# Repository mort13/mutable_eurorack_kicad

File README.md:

Mutable Instruments' Eurorack Modules.

Forked from pichenettes' version and identical except:
- Eagle brd and sch files converted to XML (making possible import into KiCad)
- For some modules, KiCad versions have been added

I have updated this repo to reflect upstream changes, but I am no longer able to convert the Eagle files, so not all are available as XML.

* [Blades](http://mutable-instruments.net/modules/blades): Dual multimode filter.
* [Blinds](http://mutable-instruments.net/modules/blinds): Quad VC-polarizer.
* [Braids](http://mutable-instruments.net/modules/braids): Macro-oscillator.
* [Branches](http://mutable-instruments.net/modules/branches): Dual Bernoulli gate.
* [Clouds](http://mutable-instruments.net/modules/clouds): Texture synthesizer.
* [Ears](http://mutable-instruments.net/modules/ears): Contact microphone.
* [Edges](http://mutable-instruments.net/modules/edges): Quad chiptune digital oscillator.
* [Elements](http://mutable-instruments.net/modules/elements): Modal synthesizer.
* [Frames](http://mutable-instruments.net/modules/frames): Keyframer/mixer.
* [Grids](http://mutable-instruments.net/modules/grids): Topographic drum sequencer.
* [Kinks](http://mutable-instruments.net/modules/kinks): Utility module - rectifier, analog logic, S&H, noise.
* [Links](http://mutable-instruments.net/modules/links): Utility module - buffer, mixer.
* [Marbles](http://mutable-instruments.net/modules/marbles): Random sampler.
* [Peaks](http://mutable-instruments.net/modules/peaks): Dual trigger converter.
* [Plaits](http://mutable-instruments.net/modules/plaits): Macro oscillator.
* [Rings](http://mutable-instruments.net/modules/rings): Resonator.
* [Ripples](http://mutable-instruments.net/modules/ripples): Liquid 2-pole BP, 2-pole LP and 4-pole LP filter.
* [Shades](http://mutable-instruments.net/modules/shades): Triple attenuverter.
* [Shelves](http://mutable-instruments.net/modules/shelves): EQ filter.
* [Stages](http://mutable-instruments.net/modules/stages): Segment generator.
* [Streams](http://mutable-instruments.net/modules/streams): Dual dynamics gate.
* [Tides](http://mutable-instruments.net/modules/tides): Tidal modulator.
* [Veils](http://mutable-instruments.net/modules/veils): Quad VCA.
* [Volts](http://mutable-instruments.net/modules/volts): +5V power module.
* [Warps](http://mutable-instruments.net/modules/warps): Meta-modulator.
* [Yarns](http://mutable-instruments.net/modules/yarns): MIDI interface.

License
=======

Code (AVR projects): GPL3.0.

Code (STM32F projects): MIT license.

Hardware: cc-by-sa-3.0

By: Emilie Gillet (emilie.o.gillet@gmail.com)

Guidelines for derivative works
===============================

**Mutable Instruments is a registered trademark.**

The name "Mutable Instruments" should not be used on any of the derivative works you create from these files.

We do not recommend you to keep the original name of the Mutable Instruments module for your derivative works.

For example, your 5U adaptation of Mutable Instruments Clouds can be called "Foobar Modular - Particle Generator".

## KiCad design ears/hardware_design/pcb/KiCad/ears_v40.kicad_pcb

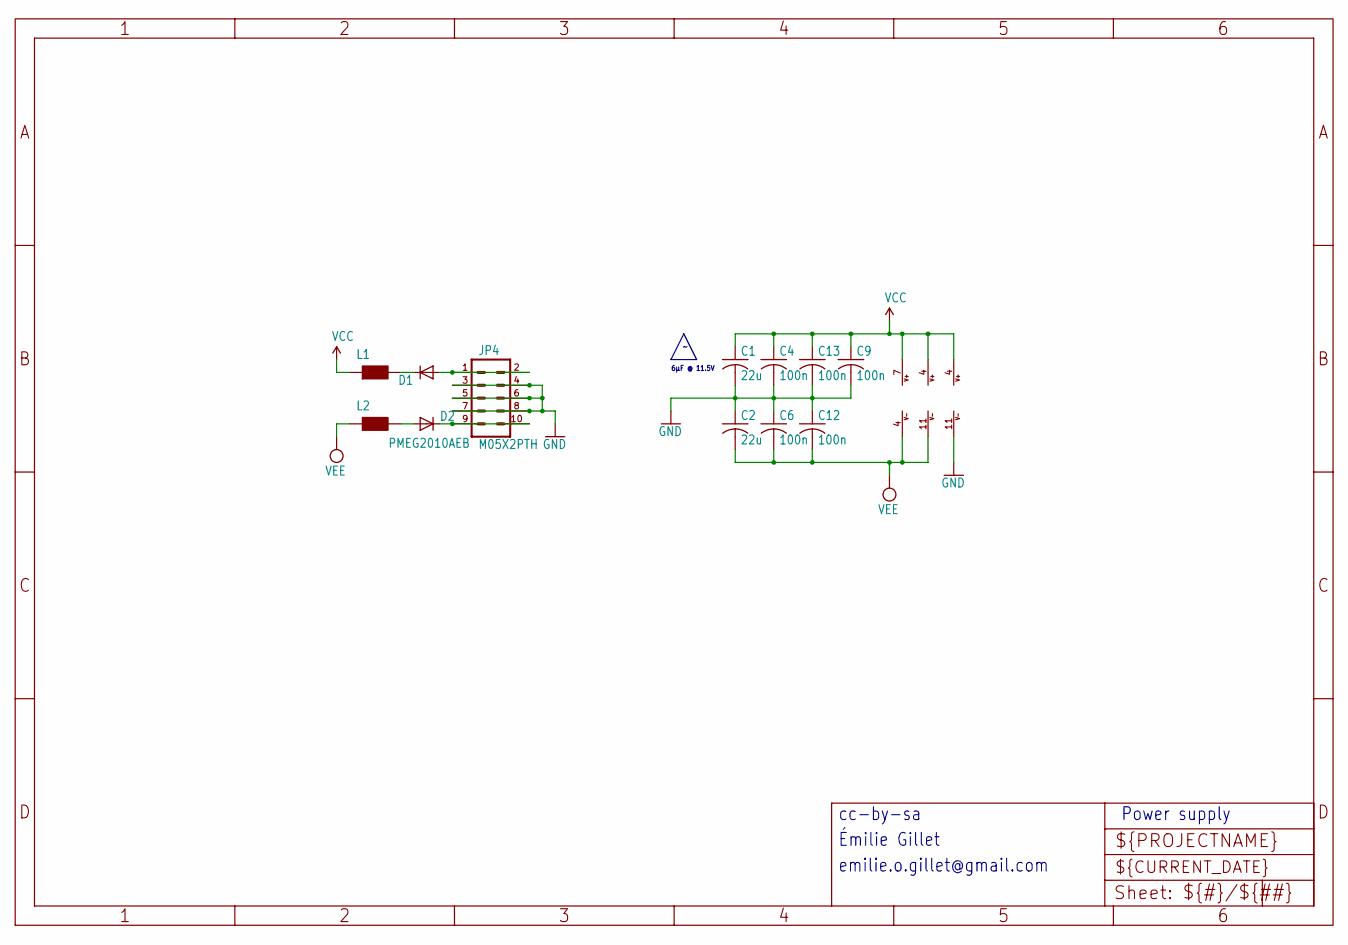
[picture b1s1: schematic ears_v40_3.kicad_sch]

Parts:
C1, C2: 22u; C1206
C4, C6, C9, C12, C13: 100n; C0402
D1, D2: PMEG2010AEB; SOD523
IC1: OPA1641; MSOP8
IC2, IC3: LM324PW; TSSOP14
JP4: M05X2PTH; AVR_ICSP
L1, L2: WE-CBF_0603; 0603

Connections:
GND: C1.2, C2.1, C4.2, C6.1, C9.2, C12.1, C13.2, IC2.11 (V-), JP4.3, JP4.4, JP4.5, JP4.6, JP4.7, JP4.8; also elsewhere on the board
unnamed: D1.A, JP4.1, JP4.2
unnamed: D2.C, JP4.9, JP4.10
unnamed: D1.C, L1.2
unnamed: D2.A, L2.2
VCC: C1.1, C4.1, C9.1, C13.1, IC1.7 (V+), IC2.4 (V+), IC3.4 (V+), L1.1; also elsewhere on the board
VEE: C2.2, C6.2, C12.2, IC1.4 (V-), IC3.11 (V-), L2.1; also elsewhere on the board

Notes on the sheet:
6µF @ 11.5V
cc-by-sa
emilie.o.gillet@gmail.com
Émilie Gillet
Power supply

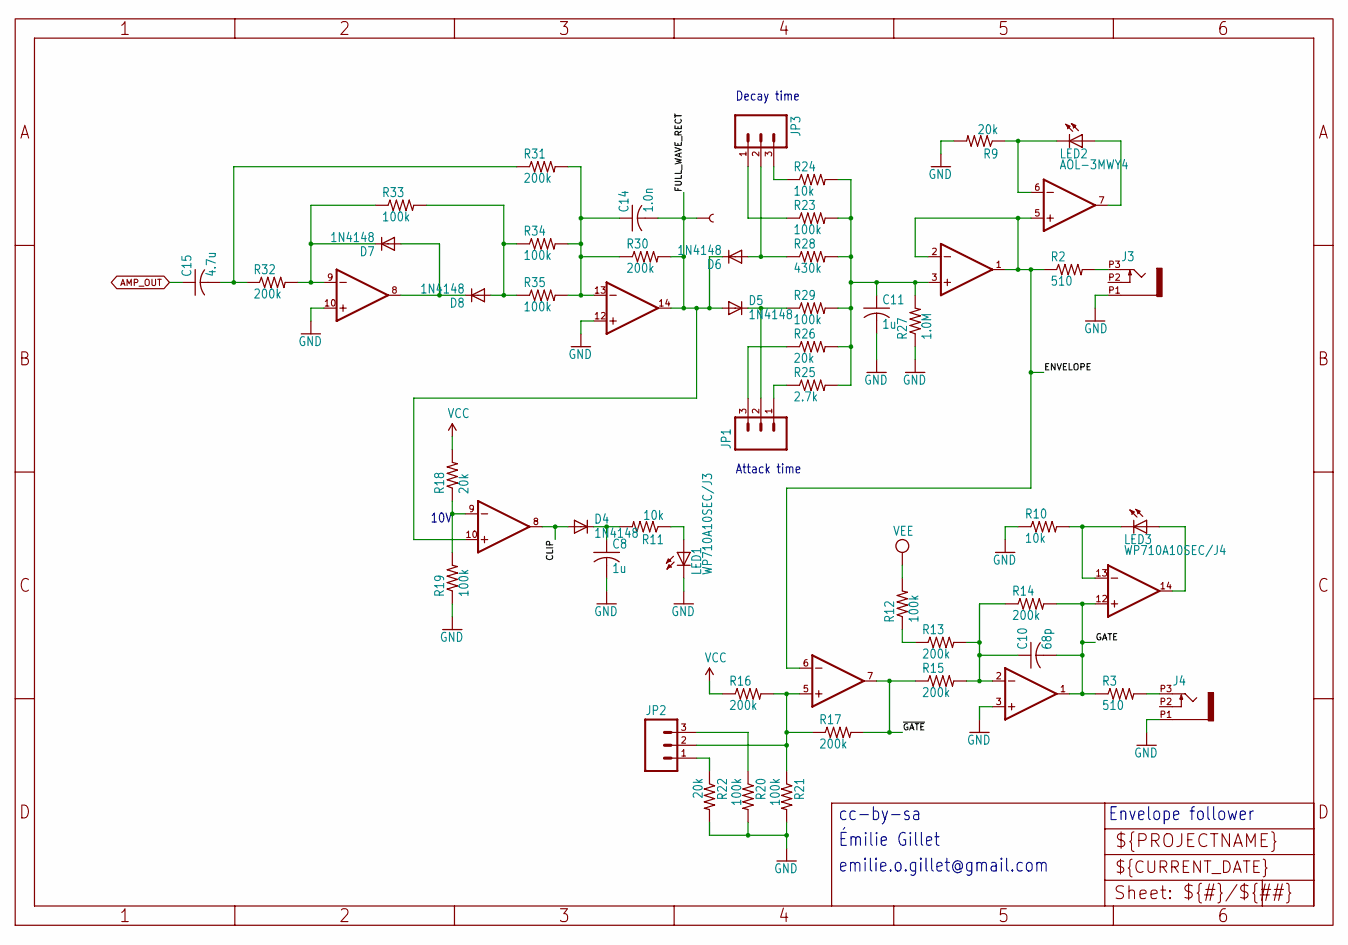
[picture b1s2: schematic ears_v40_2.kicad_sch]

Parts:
C8, C11: 1u; C0402
C10: 68p; C0402
C14: 1.0n; C0402
C15: 4.7u; C0603
D4, D5, D6, D7, D8: 1N4148; SOD523
IC2, IC3: LM324PW; TSSOP14
J3, J4: PJ301_THONKICONN6; WQP_PJ_301M6
JP1, JP2, JP3: M03PTH; 1X03
LED1: WP710A10SEC/J3; LED3MM
LED2: AOL-3MWY4; LED3MM
LED3: WP710A10SEC/J4; LED3MM
R2, R3: 510; R0402
R9, R18, R22, R26: 20k; R0402
R10, R11, R24: 10k; R0402
R12, R19, R20, R21, R23, R29, R33, R34, R35: 100k; R0402
R13, R14, R15, R16, R17, R30, R31, R32: 200k; R0402
R25: 2.7k; R0402
R27: 1.0M; R0402
R28: 430k; R0402
TP1: TEST-POINT3X5; PAD.03X.05

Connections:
AMP_OUT: C15.1; also elsewhere on the board
AMP_OUT_AC: C15.2, R31.1, R32.1
CLIP: D4.A, IC2.8 (OUT)
ENVELOPE: IC2.6 (-IN), IC3.1 (OUT), IC3.2 (-IN), IC3.5 (+IN), R2.1
FULL_WAVE_RECT: C14.2, D5.A, D6.C, IC2.10 (+IN), IC3.14 (OUT), R30.2, TP1.P$1
GATE: C10.2, IC2.1 (OUT), IC2.12 (+IN), R3.1, R14.2
GND: C8.2, C11.2, IC2.3 (+IN), IC3.10 (+IN), IC3.12 (+IN), J3.P1 (1), J4.P1 (1), LED1.K (C), R9.2, R10.1, R19.1, R20.2, R21.2, R22.2, R27.1; also elsewhere on the board
unnamed: D7.A, D8.C, IC3.8 (OUT)
unnamed: C10.1, IC2.2 (-IN), R13.2, R14.1, R15.2
unnamed: D7.C, IC3.9 (-IN), R32.2, R33.1
unnamed: D8.A, R33.2, R34.1, R35.1
unnamed: C14.1, IC3.13 (-IN), R30.1, R31.2, R34.2, R35.2
unnamed: J3.P3 (3), R2.2
unnamed: IC3.6 (-IN), LED2.K (C), R9.1
unnamed: D5.C, JP1.2, R29.1
unnamed: C11.1, IC3.3 (+IN), R23.2, R24.2, R25.2, R26.2, R27.2, R28.2, R29.2
unnamed: JP3.3, R24.1
unnamed: JP3.1, R23.1
unnamed: D6.A, JP3.2, R28.1
unnamed: JP1.1, R25.1
unnamed: JP1.3, R26.1
unnamed: IC2.9 (-IN), R18.1, R19.2
unnamed: C8.1, D4.C, R11.2
unnamed: IC3.7 (OUT), LED2.A
unnamed: LED1.A, R11.1
unnamed: J4.P3 (3), R3.2
unnamed: IC2.5 (+IN), JP2.2, R16.2, R17.1, R21.1
unnamed: JP2.1, R22.1
unnamed: JP2.3, R20.1
unnamed: IC2.13 (-IN), LED3.K (C), R10.2
unnamed: IC2.14 (OUT), LED3.A
unnamed: R12.1, R13.1
VCC: R16.1, R18.2; also elsewhere on the board
VEE: R12.2; also elsewhere on the board
~GATE: IC2.7 (OUT), R15.1, R17.2

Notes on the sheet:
cc-by-sa
10V
emilie.o.gillet@gmail.com
Émilie Gillet
Attack time
Envelope follower
Decay time

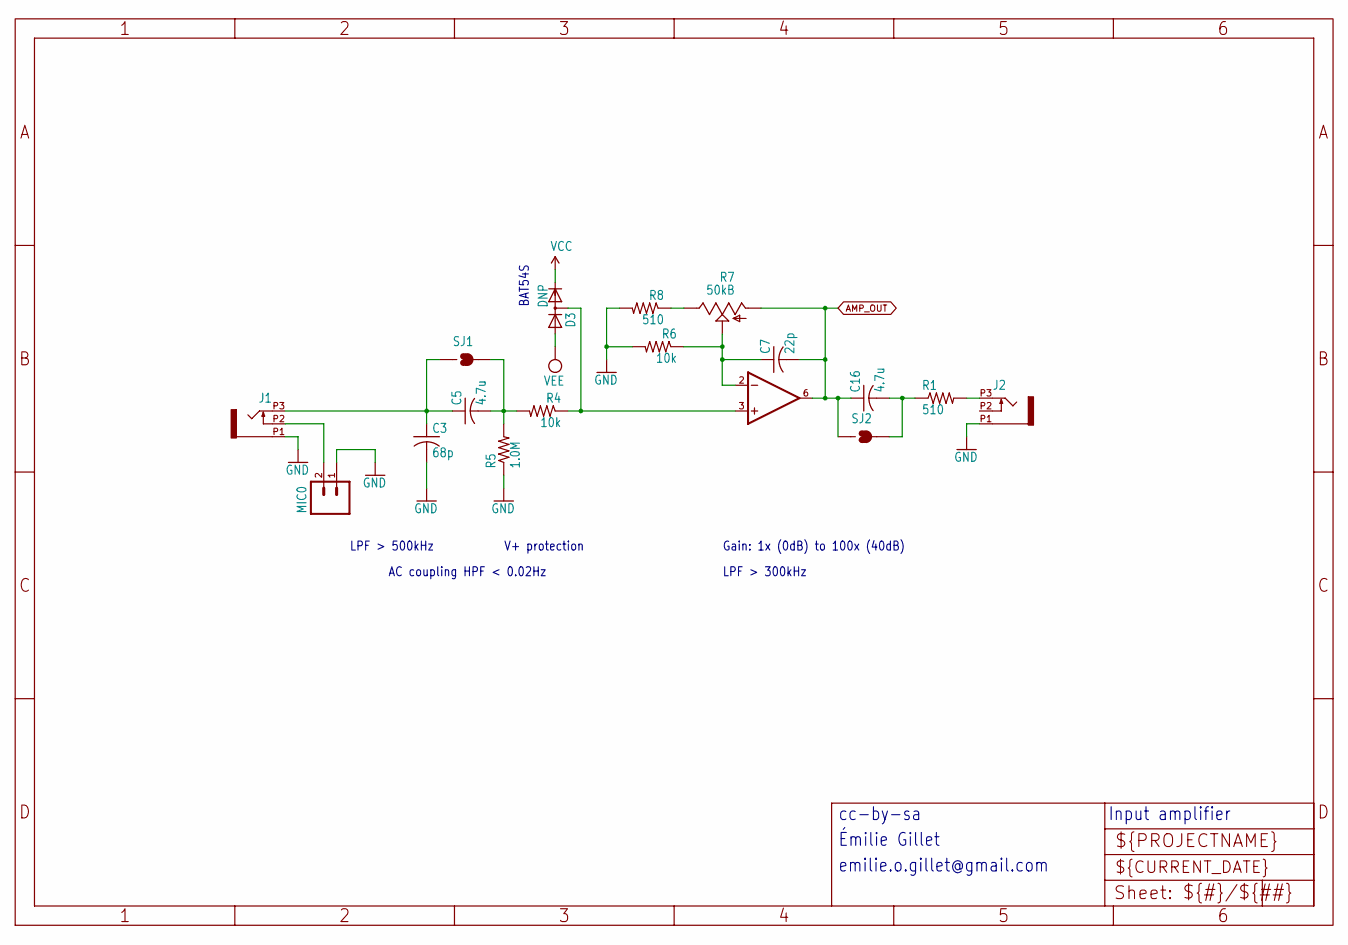
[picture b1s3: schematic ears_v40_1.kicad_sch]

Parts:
C3: 68p; C0402
C5, C16: 4.7u; C0603
C7: 22p; C0402
D3: DNP; SOT23
IC1: OPA1641; MSOP8
J1, J2: PJ301_THONKICONN6; WQP_PJ_301M6
MIC0: M02TINY; 1X02_TINY
R1, R8: 510; R0402
R4, R6: 10k; R0402
R5: 1.0M; R0402
R7: 50kB; ALPS_POT_VERTICAL_PS
SJ1, SJ2: SOLDERJUMPERNC; SJ_2S

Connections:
AMP_OUT: C7.2, C16.1, IC1.6 (OUT), R7.P$3 (A), SJ2.1; also elsewhere on the board
GND: C3.2, J1.P1 (1), J2.P1 (1), MIC0.1, R5.1, R6.2, R8.2; also elsewhere on the board
unnamed: D3.3 (AC), IC1.3 (+IN), R4.1
unnamed: J2.P3 (3), R1.2
unnamed: C3.1, C5.1, J1.P3 (3), SJ1.1
unnamed: J1.P2 (2), MIC0.2
unnamed: C7.1, IC1.2 (-IN), R6.1, R7.P$2 (S)
unnamed: C5.2, R4.2, R5.2, SJ1.2
unnamed: R7.P$1 (E), R8.1
unnamed: C16.2, R1.1, SJ2.2
VCC: D3.2 (C); also elsewhere on the board
VEE: D3.1 (A); also elsewhere on the board

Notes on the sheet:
BAT54S
LPF > 500kHz
AC coupling HPF < 0.02Hz
emilie.o.gillet@gmail.com
LPF > 300kHz
Input amplifier
Gain: 1x (0dB) to 100x (40dB)
Émilie Gillet
cc-by-sa
V+ protection

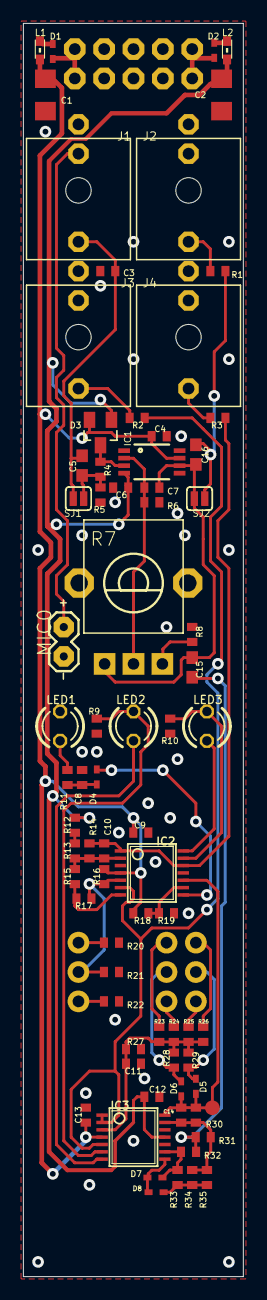
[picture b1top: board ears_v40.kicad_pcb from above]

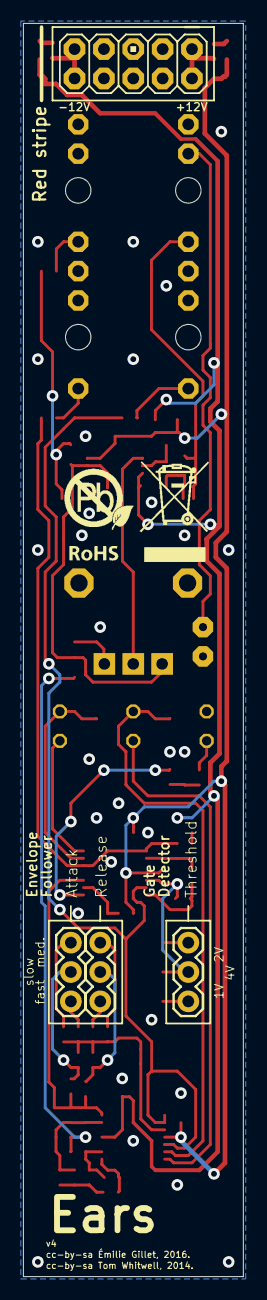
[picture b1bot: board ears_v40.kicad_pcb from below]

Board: 2 copper layers, 19.0 x 108.4 mm, 80 parts (5 on the bottom side), 47 nets.

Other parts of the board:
U$2: ROHS

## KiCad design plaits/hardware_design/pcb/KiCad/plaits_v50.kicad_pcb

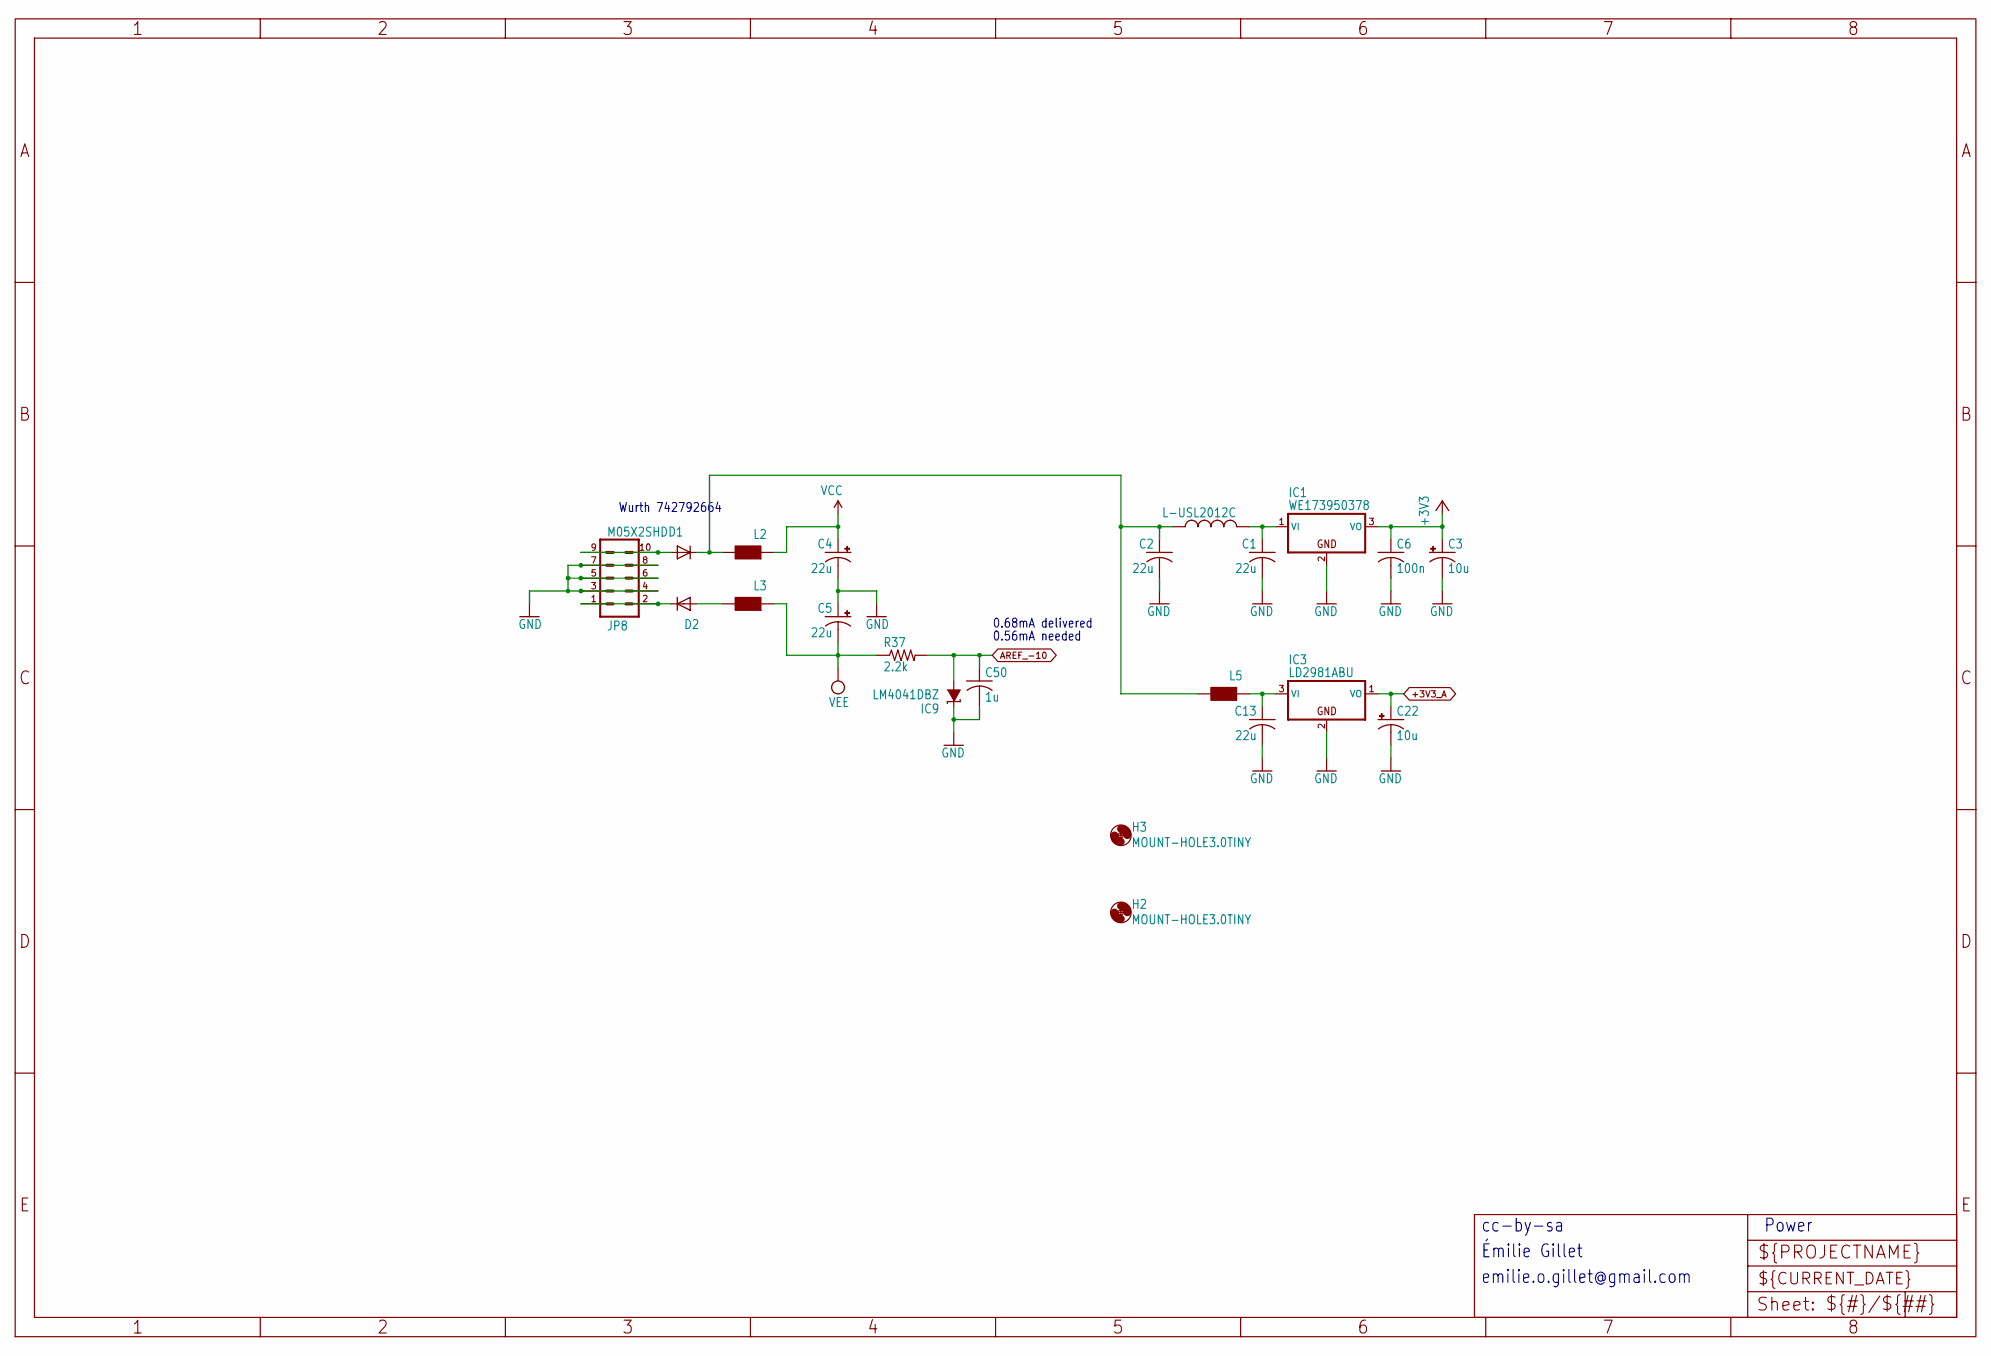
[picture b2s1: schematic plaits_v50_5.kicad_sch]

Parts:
C1, C2, C13: 22u; C1206
C3, C22: 10u; PANASONIC_A
C4, C5: 22u; PANASONIC_B
C6: 100n; C0402
C50: 1u; C0402
D1, D2: 1N5819HW; SOD123
H2, H3: MOUNT-HOLE3.0TINY; 3,0TINY
IC1: WE173950378; WE78
IC3: LD2981ABU; SOT89
IC9: LM4041DBZ; DBZ_R-PDSO-G3
JP8: M05X2SHD; 2X5-SHROUDED
L1: L-USL2012C; L2012C
L2, L3, L5: WE-CBF_0603; 0603
R37: 2.2k; R0402

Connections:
+3V3: C3.+, C6.1, IC1.3 (VO); also elsewhere on the board
+3V3_A: C22.+, IC3.1 (VO); also elsewhere on the board
AREF_-10: C50.1, IC9.2 (A), R37.2; also elsewhere on the board
GND: C1.2, C2.2, C3.-, C4.-, C5.+, C6.2, C13.2, C22.-, C50.2, IC1.2 (GND), IC3.2 (GND), IC9.1 (C), JP8.3, JP8.4, JP8.5, JP8.6, JP8.7, JP8.8; also elsewhere on the board
unnamed: C1.1, IC1.1 (VI), L1.2
unnamed: D2.A, L3.2
unnamed: C2.1, D1.C, L1.1, L2.2, L5.2
unnamed: C13.1, IC3.3 (VI), L5.1
unnamed: D1.A, JP8.9, JP8.10
unnamed: D2.C, JP8.1, JP8.2
VCC: C4.+, L2.1; also elsewhere on the board
VEE: C5.-, L3.1, R37.1; also elsewhere on the board

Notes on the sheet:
emilie.o.gillet@gmail.com
Émilie Gillet
Wurth 742792664
cc-by-sa
Power
0.68mA delivered
0.56mA needed

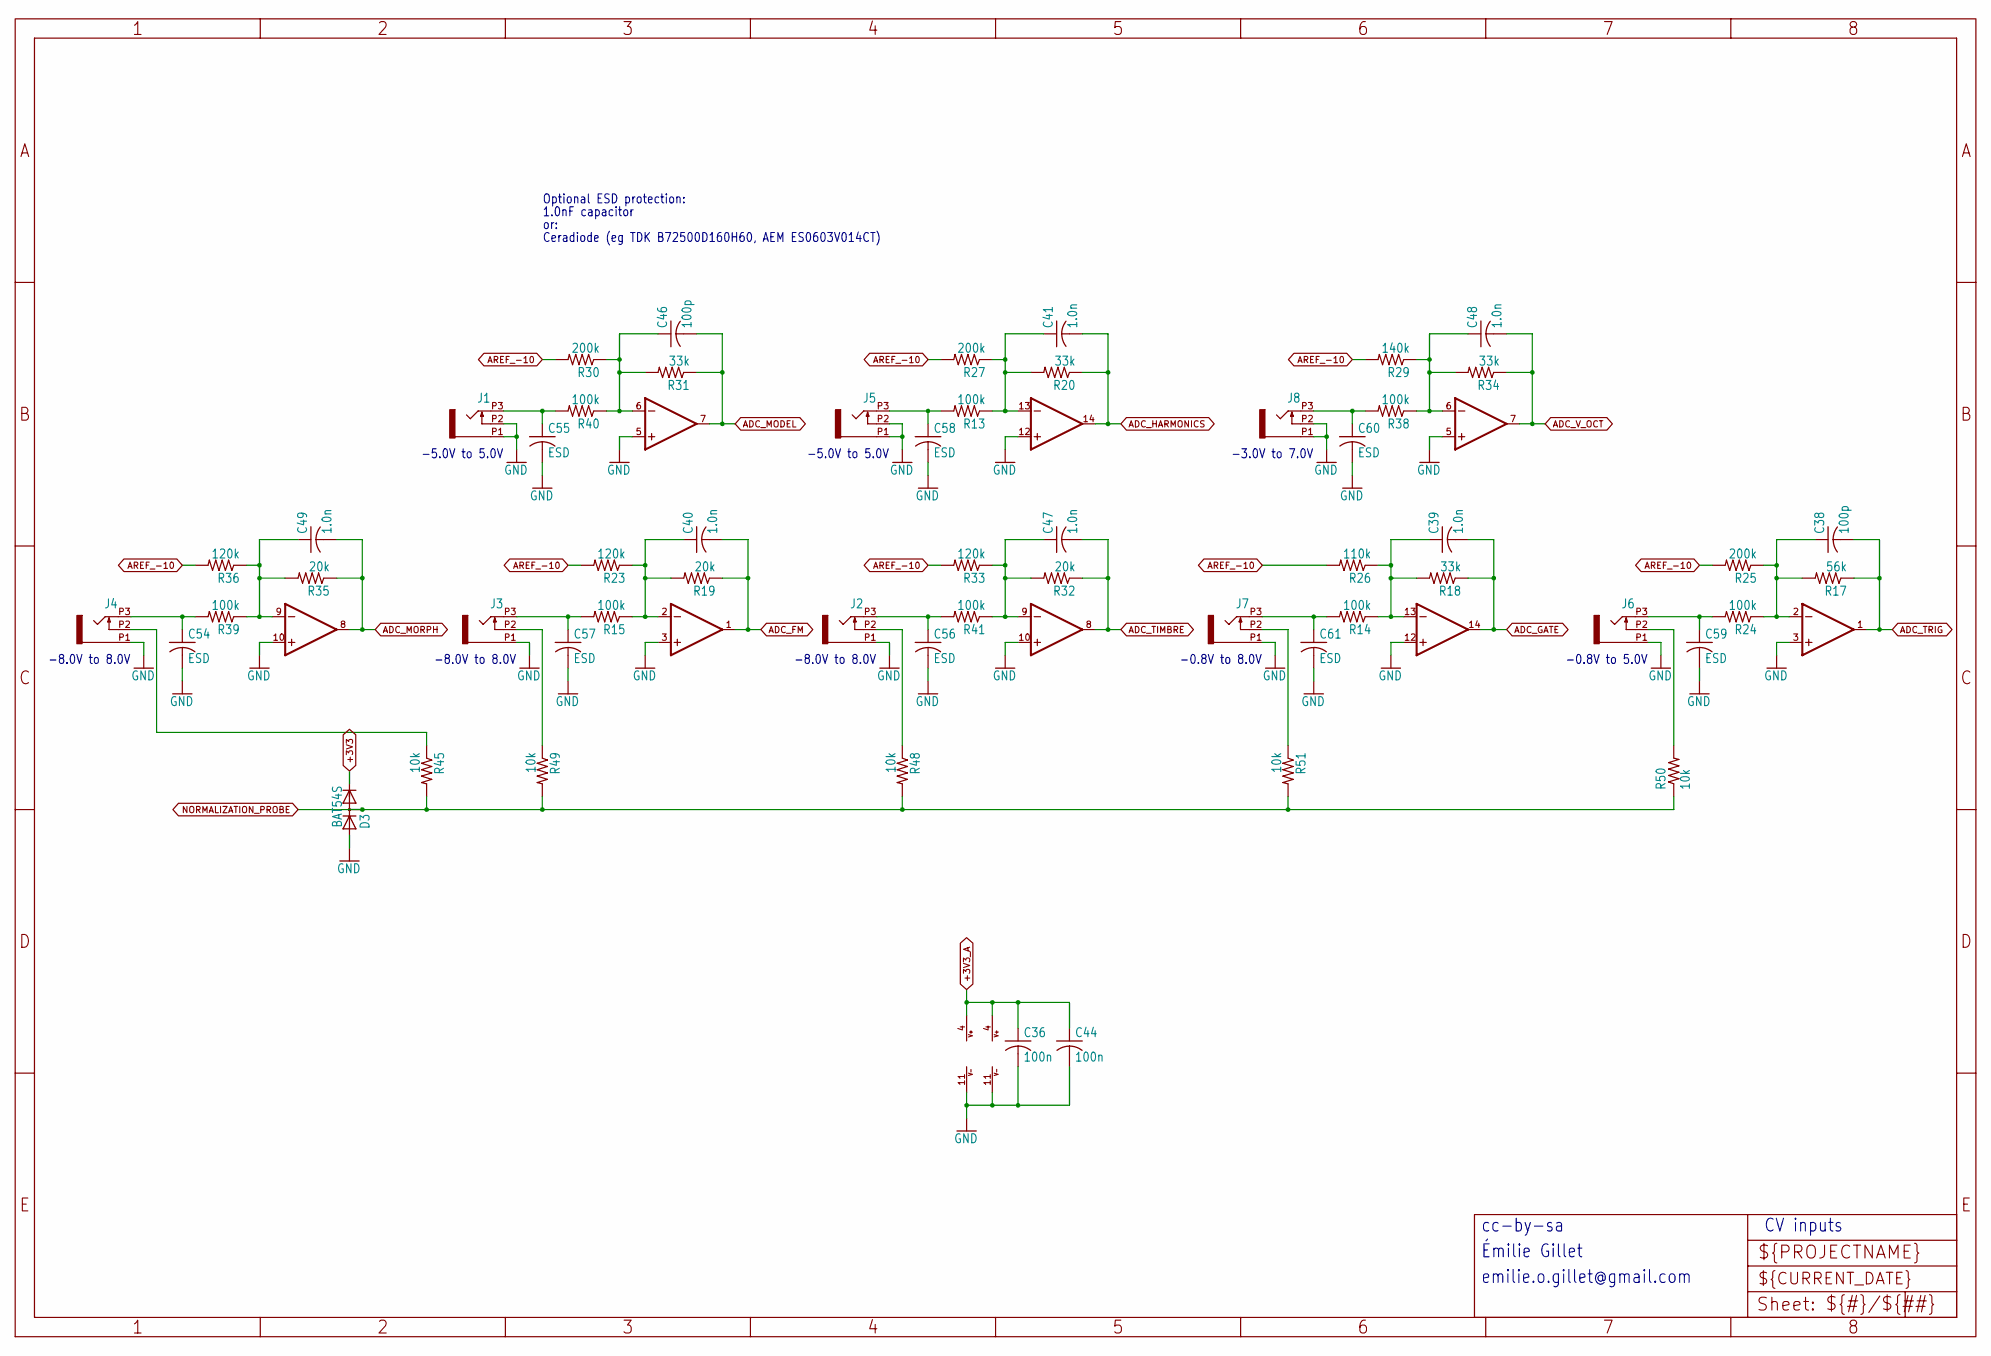
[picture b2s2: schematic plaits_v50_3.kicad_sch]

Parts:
C36, C44: 100n; C0402
C38, C46: 100p; C0402
C39, C40, C41, C47, C48, C49: 1.0n; C0402
C54, C55, C56, C57, C58, C59, C60, C61: ESD; C0603
D3: BAT54S; SOT23
IC6, IC7: TL074PW; TSSOP14_065
J1, J2, J3, J4, J5, J6, J7, J8: PJ301_THONKICONN6; WQP_PJ_301M6
R13, R14, R15, R24, R38, R39, R40, R41: 100k; R0402
R17: 56k; R0402
R18, R20, R31, R34: 33k; R0402
R19, R32, R35: 20k; R0402
R23, R33, R36: 120k; R0402
R25, R27, R30: 200k; R0402
R26: 110k; R0402
R29: 140k; R0402
R45, R48, R49, R50, R51: 10k; R0402

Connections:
+3V3: D3.2 (C); also elsewhere on the board
+3V3_A: C36.1, C44.1, IC6.4 (V+), IC7.4 (V+); also elsewhere on the board
ADC_FM: C40.2, IC7.1 (OUT), R19.1; also elsewhere on the board
ADC_GATE: C39.2, IC6.14 (OUT), R18.1; also elsewhere on the board
ADC_HARMONICS: C41.2, IC7.14 (OUT), R20.1; also elsewhere on the board
ADC_MODEL: C46.2, IC6.7 (OUT), R31.1; also elsewhere on the board
ADC_MORPH: C49.2, IC7.8 (OUT), R35.1; also elsewhere on the board
ADC_TIMBRE: C47.2, IC6.8 (OUT), R32.1; also elsewhere on the board
ADC_TRIG: C38.2, IC6.1 (OUT), R17.1; also elsewhere on the board
ADC_V_OCT: C48.2, IC7.7 (OUT), R34.1; also elsewhere on the board
AREF_-10: R23.2, R25.2, R26.2, R27.2, R29.2, R30.2, R33.2, R36.2; also elsewhere on the board
FM_IN: C57.1, J3.P3 (3), R15.2
GATE_IN: C61.1, J7.P3 (3), R14.2
GATE_IN1: C59.1, J6.P3 (3), R24.2
GND: C36.2, C44.2, C54.2, C55.2, C56.2, C57.2, C58.2, C59.2, C60.2, C61.2, D3.1 (A), IC6.3 (+IN), IC6.5 (+IN), IC6.10 (+IN), IC6.11 (V-), IC6.12 (+IN), IC7.3 (+IN), IC7.5 (+IN), IC7.10 (+IN), IC7.11 (V-), IC7.12 (+IN), J1.P1 (1), J1.P2 (2), J2.P1 (1), J3.P1 (1), J4.P1 (1), J5.P1 (1), J5.P2 (2), J6.P1 (1), J7.P1 (1), J8.P1 (1), J8.P2 (2); also elsewhere on the board
HARMONICS_IN: C58.1, J5.P3 (3), R13.2
MODEL_IN: C55.1, J1.P3 (3), R40.2
MORPH_IN: C54.1, J4.P3 (3), R39.2
unnamed: J6.P2 (2), R50.2
unnamed: C38.1, IC6.2 (-IN), R17.2, R24.1, R25.1
unnamed: J3.P2 (2), R49.1
unnamed: J2.P2 (2), R48.1
unnamed: J4.P2 (2), R45.1
unnamed: C39.1, IC6.13 (-IN), R14.1, R18.2, R26.1
unnamed: C48.1, IC7.6 (-IN), R29.1, R34.2, R38.1
unnamed: C56.1, J2.P3 (3), R41.2
unnamed: C49.1, IC7.9 (-IN), R35.2, R36.1, R39.1
unnamed: C40.1, IC7.2 (-IN), R15.1, R19.2, R23.1
unnamed: J7.P2 (2), R51.1
unnamed: C46.1, IC6.6 (-IN), R30.1, R31.2, R40.1
unnamed: C47.1, IC6.9 (-IN), R32.2, R33.1, R41.1
unnamed: C41.1, IC7.13 (-IN), R13.1, R20.2, R27.1
NORMALIZATION_PROBE: D3.3 (AC), R45.2, R48.2, R49.2, R50.1, R51.2; also elsewhere on the board
V_OCT_IN: C60.1, J8.P3 (3), R38.2

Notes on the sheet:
Émilie Gillet
-8.0V to 8.0V
CV inputs
Optional ESD protection:
or:
emilie.o.gillet@gmail.com
cc-by-sa
-5.0V to 5.0V
-3.0V to 7.0V
Ceradiode (eg TDK B72500D160H60, AEM ES0603V014CT)
-0.8V to 5.0V
1.0nF capacitor
-0.8V to 8.0V

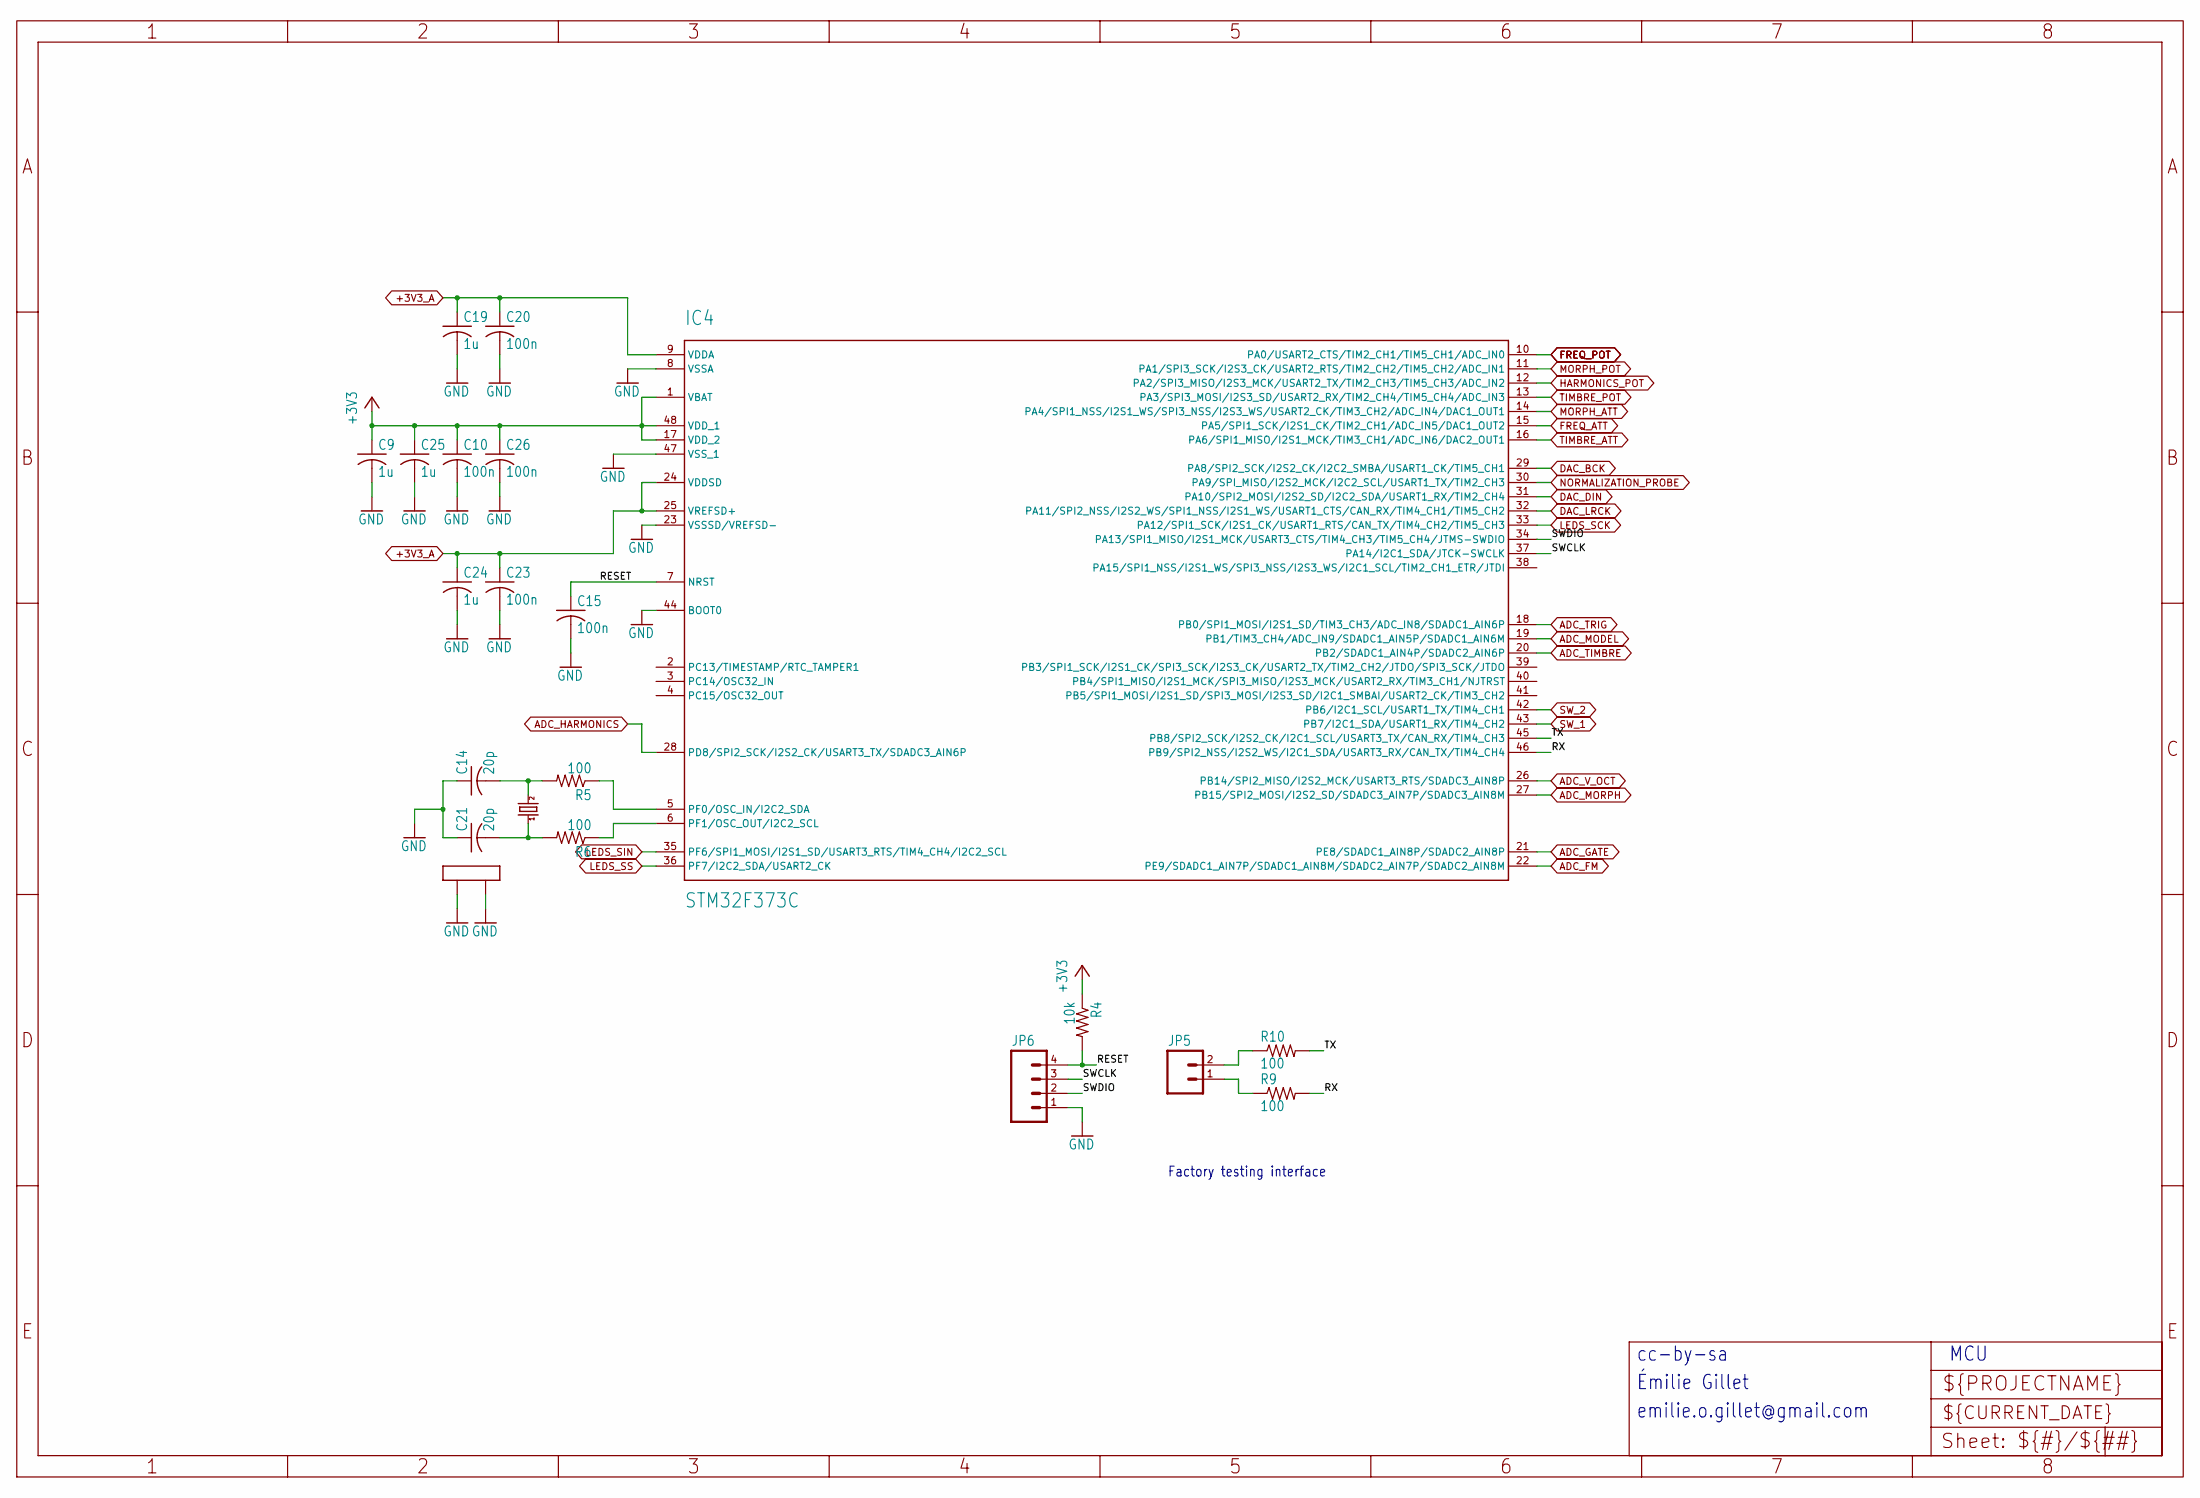
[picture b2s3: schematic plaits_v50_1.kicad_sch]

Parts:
C9, C19, C24, C25: 1u; C0402
C10, C15, C20, C23, C26: 100n; C0402
C14, C21: 20p; C0402
IC4: STM32F373C; LQFP48
JP5: M02PTH; 1X02
JP6: M04PTH; 1X04
Q1: CRYSTAL; CTS406
R4: 10k; R0402
R5, R6, R9, R10: 100; R0402

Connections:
+3V3: C9.1, C10.1, C25.1, C26.1, IC4.1 (VBAT), IC4.17 (VDD_2), IC4.48 (VDD_1), R4.1; also elsewhere on the board
+3V3_A: C19.1, C20.1, C23.1, C24.1, IC4.9 (VDDA), IC4.24 (VDDSD), IC4.25 (VREFSD+); also elsewhere on the board
ADC_FM: IC4.22 (PE9/SDADC1_AIN7P/SDADC1_AIN8M/SDADC2_AI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); also elsewhere on the board
ADC_GATE: IC4.21 (PE8/SDADC1_AIN8P/SDADC2_AIN8P); also elsewhere on the board
ADC_HARMONICS: IC4.28 (PD8/SPI2_SCK/I2S2_CK/USART3_TX/SDADC3_A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); also elsewhere on the board
ADC_MODEL: IC4.19 (PB1/TIM3_CH4/ADC_IN9/SDADC1_AIN5P/SDADC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); also elsewhere on the board
ADC_MORPH: IC4.27 (PB15/SPI2_MOSI/I2S2_SD/SDADC3_AIN7P/SDA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); also elsewhere on the board
ADC_TIMBRE: IC4.20 (PB2/SDADC1_AIN4P/SDADC2_AIN6P); also elsewhere on the board
ADC_TRIG: IC4.18 (PB0/SPI1_MOSI/I2S1_SD/TIM3_CH3/ADC_IN8/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); also elsewhere on the board
ADC_V_OCT: IC4.26 (PB14/SPI2_MISO/I2S2_MCK/USART3_RTS/SDAD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); also elsewhere on the board
DAC_BCK: IC4.29 (PA8/SPI2_SCK/I2S2_CK/I2C2_SMBA/USART1_C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); also elsewhere on the board
DAC_DIN: IC4.31 (PA10/SPI2_MOSI/I2S2_SD/I2C2_SDA/USART1_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); also elsewhere on the board
DAC_LRCK: IC4.32 (PA11/SPI2_NSS/I2S2_WS/SPI1_NSS/I2S1_WS/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); also elsewhere on the board
FREQ_ATT: IC4.15 (PA5/SPI1_SCK/I2S1_CK/TIM2_CH1/ADC_IN5/D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); also elsewhere on the board
FREQ_POT: IC4.10 (PA0/USART2_CTS/TIM2_CH1/TIM5_CH1/ADC_IN0); also elsewhere on the board
GND: C9.2, C10.2, C14.1, C15.2, C19.2, C20.2, C21.1, C23.2, C24.2, C25.2, C26.2, IC4.8 (VSSA), IC4.23 (VSSSD/VREFSD-), IC4.44 (BOOT0), IC4.47 (VSS_1), JP6.1, Q1.2 (LID1), Q1.4 (LID2); also elsewhere on the board
HARMONICS_POT: IC4.12 (PA2/SPI3_MISO/I2S3_MCK/USART2_TX/TIM2_C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); also elsewhere on the board
LEDS_SCK: IC4.33 (PA12/SPI1_SCK/I2S1_CK/USART1_RTS/CAN_TX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); also elsewhere on the board
LEDS_SIN: IC4.35 (PF6/SPI1_MOSI/I2S1_SD/USART3_RTS/TIM4_C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); also elsewhere on the board
LEDS_SS: IC4.36 (PF7/I2C2_SDA/USART2_CK); also elsewhere on the board
MORPH_ATT: IC4.14 (PA4/SPI1_NSS/I2S1_WS/SPI3_NSS/I2S3_WS/U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); also elsewhere on the board
MORPH_POT: IC4.11 (PA1/SPI3_SCK/I2S3_CK/USART2_RTS/TIM2_CH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); also elsewhere on the board
unnamed: IC4.5 (PF0/OSC_IN/I2C2_SDA), R5.1
unnamed: IC4.6 (PF1/OSC_OUT/I2C2_SCL), R6.1
unnamed: C14.2, Q1.3 (2), R5.2
unnamed: JP5.2, R10.1
unnamed: C21.2, Q1.1, R6.2
unnamed: JP5.1, R9.1
NORMALIZATION_PROBE: IC4.30 (PA9/SPI_MISO/I2S2_MCK/I2C2_SCL/USART1_T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); also elsewhere on the board
RESET: C15.1, IC4.7 (NRST), JP6.4, R4.2
RX: IC4.46 (PB9/SPI2_NSS/I2S2_WS/I2C1_SDA/USART3_RX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), R9.2
SWCLK: IC4.37 (PA14/I2C1_SDA/JTCK-SWCLK), JP6.3
SWDIO: IC4.34 (PA13/SPI1_MISO/I2S1_MCK/USART3_CTS/TIM4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), JP6.2
SW_1: IC4.43 (PB7/I2C1_SDA/USART1_RX/TIM4_CH2); also elsewhere on the board
SW_2: IC4.42 (PB6/I2C1_SCL/USART1_TX/TIM4_CH1); also elsewhere on the board
TIMBRE_ATT: IC4.16 (PA6/SPI1_MISO/I2S1_MCK/TIM3_CH1/ADC_IN6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); also elsewhere on the board
TIMBRE_POT: IC4.13 (PA3/SPI3_MOSI/I2S3_SD/USART2_RX/TIM2_CH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); also elsewhere on the board
TX: IC4.45 (PB8/SPI2_SCK/I2S2_CK/I2C1_SCL/USART3_TX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), R10.2

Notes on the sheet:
MCU
cc-by-sa
Factory testing interface
Émilie Gillet
emilie.o.gillet@gmail.com

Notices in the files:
ears/hardware_design/pcb/KiCad/ears_v40.kicad_pcb:
cc-by-sa Tom Whitwell, 2014.
cc-by-sa Émilie Gillet, 2016.
edges/hardware_design/pcb/KiCad/edges_v20.kicad_pcb:
cc-by-sa Émilie Gillet, 2014. v2
shelves/hardware_design/pcb/KiCad/shelves_v05.kicad_pcb:
cc-by-sa Émilie Gillet, 2014. v0.5
volts/hardware_design/pcb/KiCad/volts_v01.kicad_pcb:
cc-by-sa Émilie Gillet. 2013, v0.1
warps/hardware_design/pcb/KiCad/warps_v30.kicad_pcb:
cc-by-sa Émilie Gillet, 2015. v3
